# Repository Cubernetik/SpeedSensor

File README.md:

# ESP32 Timer-Based Pulse Distance Measurement

This is the source code to test an optical sensor to measure speed by time and distance. I use it for my experimental rail gun,
specifically for auto tuning the coil timing to maximize speed. This is an experiment and will not result in a rail gun with
notable projectile energy and is a mere physics experiment.

This implementation demonstrates how to measure the distance (time difference) between two GPIO pulses using the ESP32. It uses
hardware-level timers for precise measurement and ensures correct handling of timer overflows. The solution accounts for GPIO interrupts,
timer configurations, and overflow management.

## How It Works

  - GPIO Setup: The two GPIO pins (26 and 27) are set as inputs, and interrupts are attached to both to trigger on the rising edge of the signal.
  - Interrupt Service Routines (ISRs): The ISRs capture the current time (using the timer's counter) when a rising edge is detected.
  - Timer Configuration: A timer is configured to run with 1 µs resolution, allowing precise time tracking for the pulse measurement.
  - Time Difference Calculation: When both GPIO pins trigger, the time difference is calculated using the stored timer values. The calculation
    handles the potential timer overflow, ensuring the result remains accurate.

## Future Improvements

  - Higher Precision: The system can be adapted for higher-speed measurements by increasing timer resolution or using more advanced techniques like      the RMT peripheral.

## Conclusion

## Model files
Model files for 3D printing are available here: https://makerworld.com/en/models/1217145-speed-sensor-tube#profileId-1233233

## Schematic
Schematic for the IR proximity sensor board. Schematic and board located in kicad folder.

## Example Measurements
The relative error shows room for improvement. Unfortunately lacking a RS flip flop to make a rising and a falling edge out of the two
rising edges. Once I have this done I will use RMT to count the distance of those two edges which can be done with 12.5 ns resolution
on hardware level. The precision should be sufficient after this change.
 - Time = 45332 µs, Speed = 0.662 m/s (2.38 km/h)
 - Time = 46816 µs, Speed = 0.641 m/s (2.31 km/h)
 - Time = 42106 µs, Speed = 0.712 m/s (2.56 km/h)
 - Time = 43452 µs, Speed = 0.690 m/s (2.49 km/h)

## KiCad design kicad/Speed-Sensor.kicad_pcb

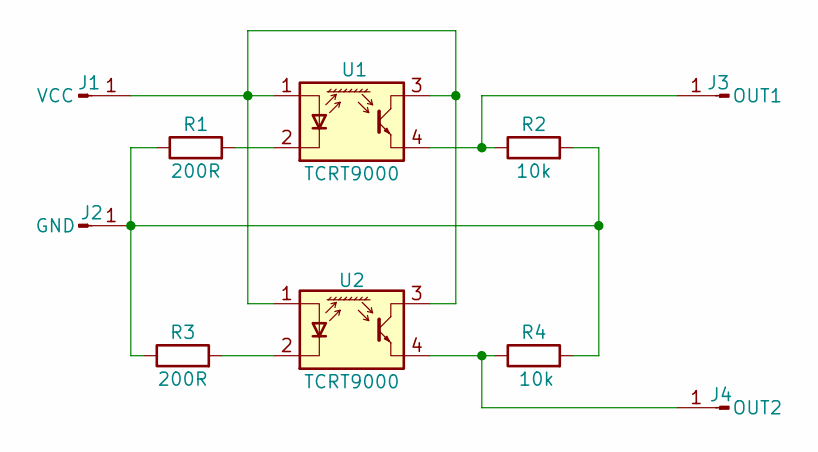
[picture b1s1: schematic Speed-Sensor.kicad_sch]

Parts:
J1: VCC; TestPoint_THTPad_2.0x2.0mm_Drill1.0mm
J2: GND; TestPoint_THTPad_2.0x2.0mm_Drill1.0mm
J3: OUT1; TestPoint_THTPad_2.0x2.0mm_Drill1.0mm
J4: OUT2; TestPoint_THTPad_2.0x2.0mm_Drill1.0mm
R1: 200R; R_Axial_DIN0204_L3.6mm_D1.6mm_P5.08mm_Horizontal
R2, R4: 10k; R_Axial_DIN0204_L3.6mm_D1.6mm_P5.08mm_Vertical
R3: 200R; R_Axial_DIN0204_L3.6mm_D1.6mm_P5.08mm_Vertical
U1, U2: TCRT9000

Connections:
unnamed: J1.1, U1.1 (A), U1.3 (C), U2.1 (A), U2.3 (C)
unnamed: J2.1, R1.1, R2.2, R3.1, R4.2
unnamed: J3.1, R2.1, U1.4 (E)
unnamed: J4.1, R4.1, U2.4 (E)
unnamed: R1.2, U1.2 (K)
unnamed: R3.2, U2.2 (K)

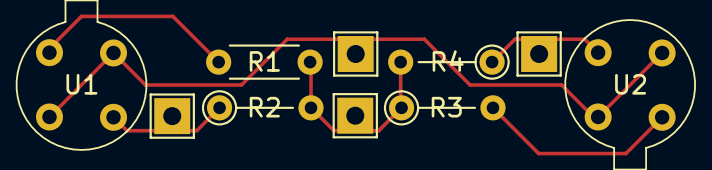
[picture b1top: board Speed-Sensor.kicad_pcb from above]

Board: 2 copper layers, 10 parts (0 on the bottom side), 6 nets.

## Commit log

2025-04-04 Add schematic for IR proximity sensors
2025-04-04 Add schematic to README.md
2025-04-04 Add kicad files for IR proximity sensor PCB
2025-04-04 Added reference to kicad files to README.md
